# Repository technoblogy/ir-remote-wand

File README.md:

# IR Remote Wand
A simple universal remote control based on an ATtiny85. For more information see http://www.technoblogy.com/show?25TN.

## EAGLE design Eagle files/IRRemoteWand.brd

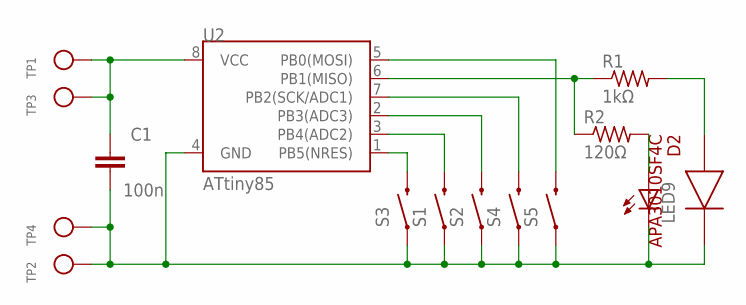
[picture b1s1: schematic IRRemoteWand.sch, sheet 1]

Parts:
C1: 100n; 0603-CAP
D2: APA3010SF4C
LED9: LEDCHIPLED_0805; CHIPLED_0805
R1: 1kΩ; M0805
R2: 120Ω; M0805
S1, S2, S3, S4, S5: SWITCH-MOMENTARY-2SMD-4; TACTILE_SWITCH_TALL
TP1, TP2, TP3, TP4: TESTPOINTPAD; TESTPOINT_PAD_2MM
U2: ATtiny85; SO08-EIAJ

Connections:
GND: C1.2, D2.2, LED9.C, S1.A2 (1), S2.A2 (1), S3.A2 (1), S4.A2 (1), S5.A2 (1), TP2.P$1, TP4.P$1, U2.4 (GND)
unnamed: R1.1, R2.1, U2.6 (PB1(MISO))
unnamed: S3.B2 (2), U2.1 (PB5(NRES))
unnamed: S1.B2 (2), U2.3 (PB4(ADC2))
unnamed: S2.B2 (2), U2.2 (PB3(ADC3))
unnamed: S4.B2 (2), U2.7 (PB2(SCK/ADC1))
unnamed: D2.1, R1.2
unnamed: S5.B2 (2), U2.5 (PB0(MOSI))
unnamed: C1.1, TP1.P$1, TP3.P$1, U2.8 (VCC)
unnamed: LED9.A, R2.2

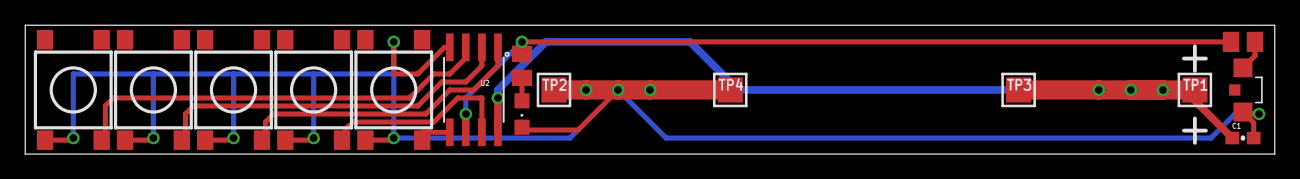
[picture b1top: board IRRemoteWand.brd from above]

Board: 2 copper layers, 99.0 x 10.2 mm, 15 parts (0 on the bottom side), 10 nets.

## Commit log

2018-05-08 Version 1 - 8th May 2018
2018-05-13 Version 2 - 13th May 2018
2021-08-09 Create Attiny85 remote transmitter

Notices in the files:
parts and their libraries:
SparkFun-Electromechanical: Licensing: Creative Commons ShareAlike 4.0 International - https://creativecommons.org/licenses/by-sa/4.0
SparkFun-Capacitors: Licensing: CC v3.0 Share-Alike You are welcome to use this library for commercial purposes.
